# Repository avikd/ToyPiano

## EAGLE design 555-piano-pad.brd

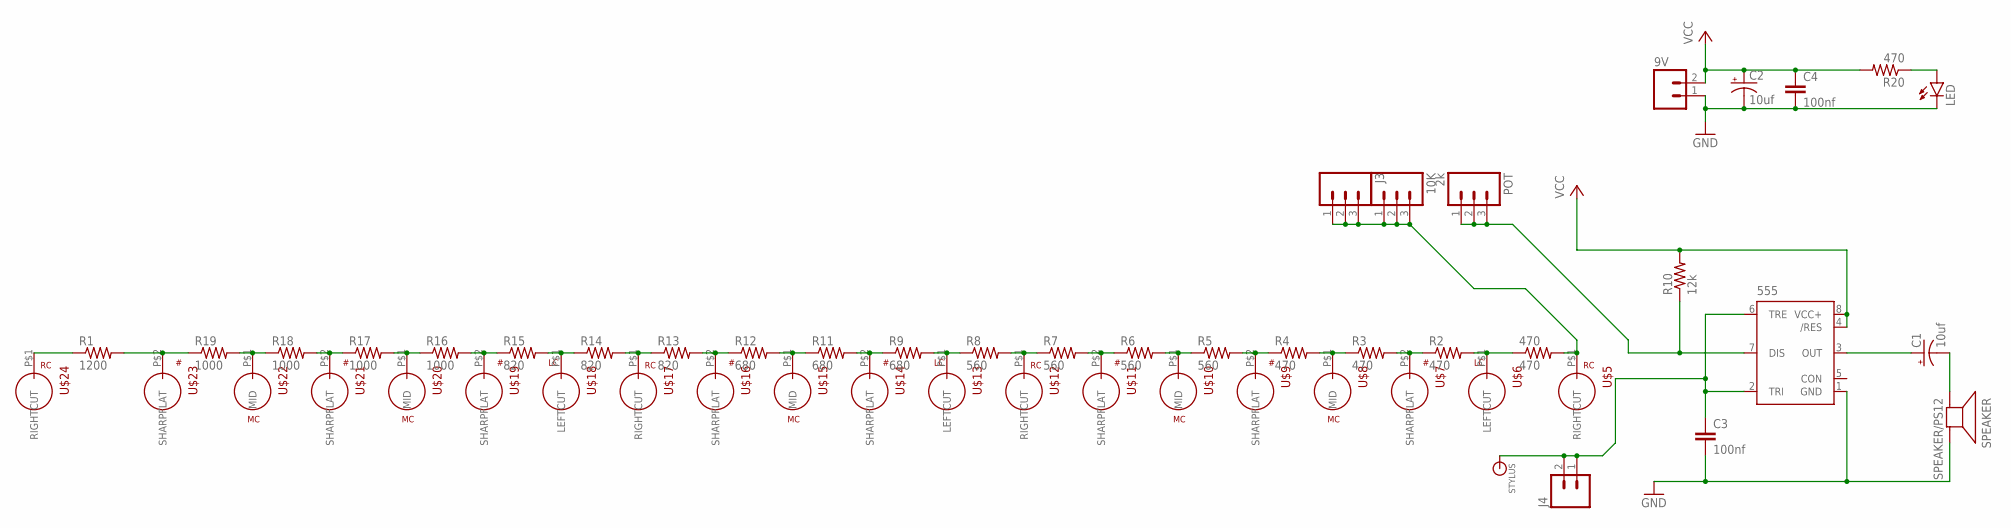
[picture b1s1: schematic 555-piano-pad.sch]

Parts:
9V: M02PTH3; 1X02_LONGPADS
10K: M03PTH; 1X03
470: 470; AXIAL-0.3
555: NE555P; DIL-08
C1, C2: 10uf; CPOL-RADIAL-10UF-25V
C3, C4: 100nf; CAP-PTH-SMALL2
J3: M03PTH; 1X03
J4: M02PTH3; 1X02_LONGPADS
LED: LED5MM
POT: 2k; 1X03
R1: 1200; AXIAL-0.3
R2, R3, R4, R20: 470; AXIAL-0.3
R5, R6, R7, R8: 560; AXIAL-0.3
R9, R11, R12: 680; AXIAL-0.3
R10: 12k; AXIAL-0.3
R13, R14, R15: 820; AXIAL-0.3
R16, R17, R18, R19: 1000; AXIAL-0.3
SPEAKER: SPEAKER/PS12; PS12
STYLUS: BANANA_CONN
U$5, U$12, U$17, U$24: PINANO-RIGHT-CUT
U$6, U$13, U$18: PINANO-LEFT-CUT
U$7, U$9, U$11, U$14, U$16, U$19, U$21, U$23: PINANO-SHARPFLAT
U$8, U$10, U$15, U$20, U$22: PINANO-MID

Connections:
GND: 9V.1, 555.1 (GND), C2.2 (-), C3.2, C4.2, LED.K (C), SPEAKER.P$2 (-)
unnamed: C1.2 (-), SPEAKER.P$1 (+)
unnamed: 10K.1, 10K.2, 10K.3, 470.P$2 (2), J3.1, J3.2, J3.3, U$5.P$1
unnamed: 470.P$1 (1), R2.P$2 (2), U$6.P$1
unnamed: R2.P$1 (1), R3.P$2 (2), U$7.P$2
unnamed: R3.P$1 (1), R4.P$2 (2), U$8.P$1
unnamed: R4.P$1 (1), R5.P$2 (2), U$9.P$2
unnamed: R5.P$1 (1), R6.P$2 (2), U$10.P$1
unnamed: 555.3 (OUT), C1.1 (+)
unnamed: R6.P$1 (1), R7.P$2 (2), U$11.P$2
unnamed: R7.P$1 (1), R8.P$2 (2), U$12.P$1
unnamed: R8.P$1 (1), R9.P$2 (2), U$13.P$1
unnamed: R9.P$1 (1), R11.P$2 (2), U$14.P$2
unnamed: R11.P$1 (1), R12.P$2 (2), U$15.P$1
unnamed: R12.P$1 (1), R13.P$2 (2), U$16.P$2
unnamed: R13.P$1 (1), R14.P$2 (2), U$17.P$1
unnamed: R14.P$1 (1), R15.P$2 (2), U$18.P$1
unnamed: R15.P$1 (1), R16.P$2 (2), U$19.P$2
unnamed: 555.2 (TRI), 555.6 (TRE), C3.1, J4.1, J4.2, STYLUS.P$1
unnamed: R16.P$1 (1), R17.P$2 (2), U$20.P$1
unnamed: 555.7 (DIS), POT.1, POT.2, POT.3, R10.P$1 (1)
unnamed: R17.P$1 (1), R18.P$2 (2), U$21.P$2
unnamed: R18.P$1 (1), R19.P$2 (2), U$22.P$1
unnamed: R1.P$2 (2), R19.P$1 (1), U$23.P$2
unnamed: R1.P$1 (1), U$24.P$1
unnamed: LED.A, R20.P$1 (1)
VCC: 9V.2, 555.4 (/RES), 555.8 (VCC+), C2.1 (+), C4.1, R10.P$2 (2), R20.P$2 (2)

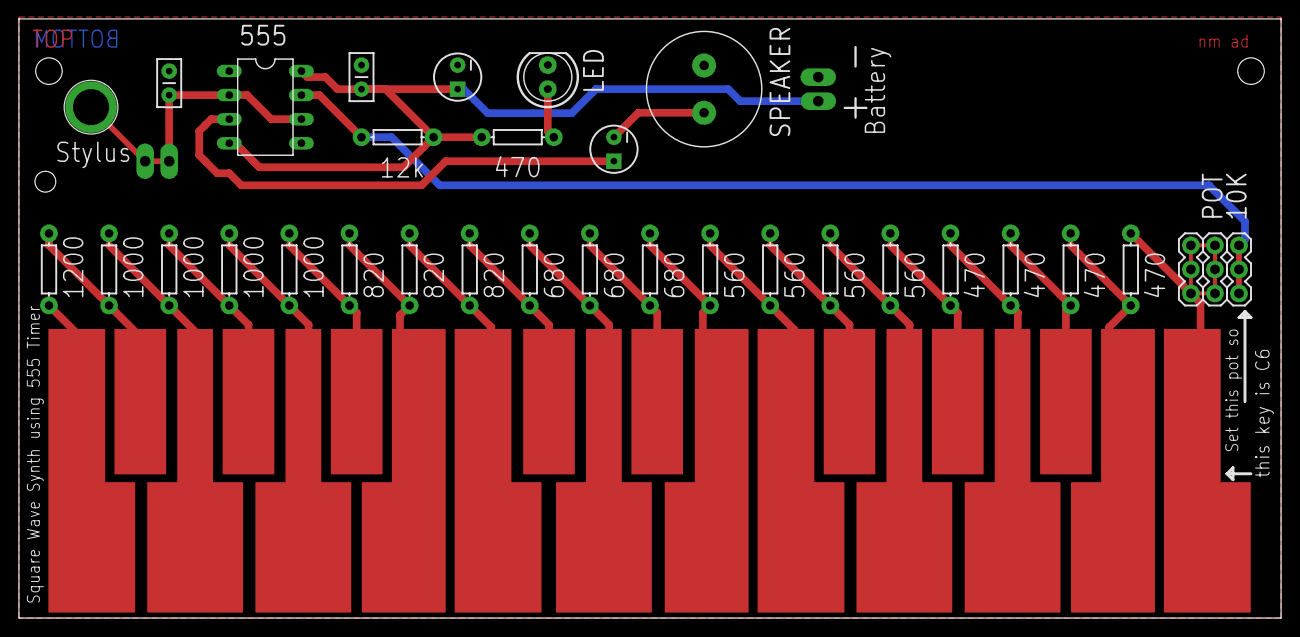
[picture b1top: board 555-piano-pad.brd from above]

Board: 2 copper layers, 133.3 x 63.3 mm, 54 parts (0 on the bottom side), 27 nets.

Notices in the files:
parts and their libraries:
SparkFun-AnalogIC: Licensing:Creative Commons ShareAlike 4.0 International - https://creativecommons.org/licenses/by-sa/4.0
